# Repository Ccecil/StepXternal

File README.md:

Board to breakout Step/Dir/EN signals from a V2 Smoothiboard.

Config example: https://github.com/Smoothieware/SmoothieV2/blob/master/ConfigSamples/external-drivers.ini

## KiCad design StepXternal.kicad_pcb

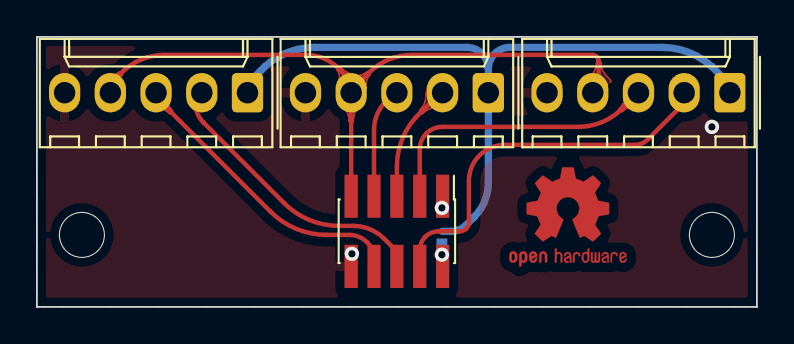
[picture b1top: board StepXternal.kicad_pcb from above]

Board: 2 copper layers, 40.0 x 15.0 mm, 5 parts (1 on the bottom side), 11 nets.

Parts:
J1: Conn_02x05_Odd_Even; PinHeader_2x05_P1.27mm_Vertical_SMD
J2, J3, J4: Conn_01x05_Male; Molex_KK-254_AE-6410-05A_1x05_P2.54mm_Vertical
JP1: SolderJumper_3_Bridged12; SolderJumper-3_P1.3mm_Bridged12_RoundedPad1.0x1.5mm

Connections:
+3V3: J1.1, JP1.3 (B)
+5V: J1.2, JP1.1 (A)
+V: J2.1, J3.1, J4.1, JP1.2 (C)
DIR1: J1.3, J2.3
DIR2: J1.7, J3.3
DIR3: J1.8, J4.3
EN: J1.9, J2.4, J3.4, J4.4
GND: J1.10, J2.5, J3.5, J4.5
STP1: J1.4, J2.2
STP2: J1.5, J3.2
STP3: J1.6, J4.2
